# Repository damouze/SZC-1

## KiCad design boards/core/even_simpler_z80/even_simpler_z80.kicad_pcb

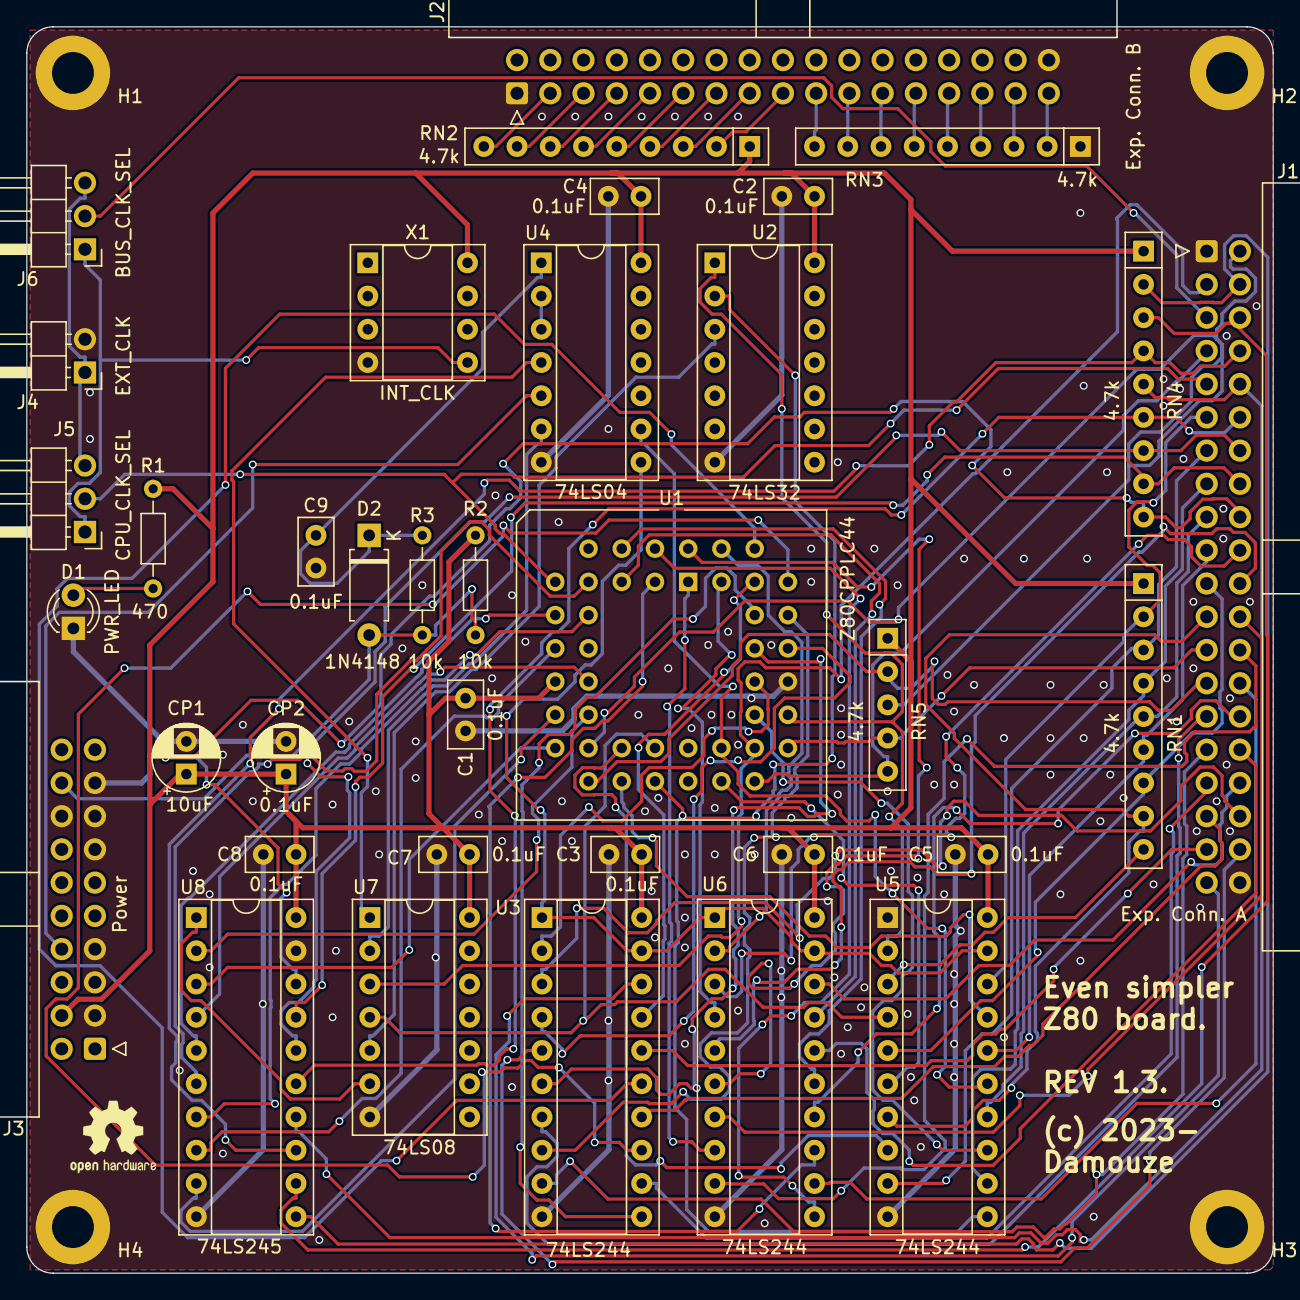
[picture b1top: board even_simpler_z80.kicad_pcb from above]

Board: 2 copper layers, 95.2 x 95.2 mm, 40 parts (0 on the bottom side), 101 nets.

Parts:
C1, C2, C3, C4, C5, C6, C7, C8, C9: 0.1uF; C_Disc_D5.0mm_W2.5mm_P2.50mm
CP1: 10uF; CP_Radial_D5.0mm_P2.50mm
CP2: 0.1uF; CP_Radial_D5.0mm_P2.50mm
D1: PWR_LED; LED_D3.0mm
D2: 1N4148; D_A-405_P7.62mm_Horizontal
H1, H2, H3, H4: MountingHole_Pad; MountingHole_3.2mm_M3_ISO7380_Pad
J1: Exp. Conn. A; IDC-Header_2x20_P2.54mm_Horizontal
J2: Exp. Conn. B; IDC-Header_2x17_P2.54mm_Horizontal
J3: Power; IDC-Header_2x10_P2.54mm_Horizontal
J4: EXT_CLK; PinHeader_1x02_P2.54mm_Horizontal
J5: CPU_CLK_SEL; PinHeader_1x03_P2.54mm_Horizontal
J6: BUS_CLK_SEL; PinHeader_1x03_P2.54mm_Horizontal
R1: 470; R_Axial_DIN0204_L3.6mm_D1.6mm_P7.62mm_Horizontal
R2, R3: 10k; R_Axial_DIN0204_L3.6mm_D1.6mm_P7.62mm_Horizontal
RN1, RN2, RN3, RN4: 4.7k; R_Array_SIP9
RN5: 4.7k; R_Array_SIP5
U1: Z80CPPLC44; PLCC-44_THT-Socket
U2: 74LS32; DIP-14_W7.62mm_Socket
U3, U5, U6: 74LS244; DIP-20_W7.62mm_Socket
U4: 74LS04; DIP-14_W7.62mm_Socket
U7: 74LS08; DIP-14_W7.62mm_Socket
U8: 74LS245; DIP-20_W7.62mm_Socket
X1: INT_CLK; DIP-8_W7.62mm_Socket

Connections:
/+5V: C1.1, C2.1, C3.1, C4.1, C5.1, C6.1, C7.1, C8.1, CP1.1, CP2.1, J3.4, R1.1, R2.1, RN1.1 (common), RN2.1 (common), RN4.1 (common), RN5.1 (common), U1.13 (VCC), U2.14 (VCC), U3.20 (VCC), U4.14 (VCC), U5.20 (VCC), U6.20 (VCC), U7.14 (VCC), U8.20 (VCC), X1.8 (Vcc)
/BUS_CLK: J1.5, J6.2
/B_A0: J1.39, U3.18 (O0a)
/B_A1: J1.37, U3.16 (O1a)
/B_A2: J1.35, U3.14 (O2a)
/B_A3: J1.33, U3.12 (O3a)
/B_A4: J1.31, U3.9 (O0b)
/B_A5: J1.29, U3.7 (O1b)
/B_A6: J1.38, U3.5 (O2b)
/B_A7: J1.36, U3.3 (O3b)
/B_A8: J1.34, U6.18 (O0a)
/B_A9: J1.32, U6.16 (O1a)
/B_A10: J1.30, U6.14 (O2a)
/B_A11: J1.28, U6.12 (O3a)
/B_A12: J1.26, U6.9 (O0b)
/B_A13: J1.24, U6.7 (O1b)
/B_A14: J1.22, U6.5 (O2b)
/B_A15: J1.20, U6.3 (O3b)
/B_D0: J1.18, RN4.9 (R8), U8.18 (B0)
/B_D1: J1.16, RN4.8 (R7), U8.17 (B1)
/B_D2: J1.14, RN4.7 (R6), U8.16 (B2)
/B_D3: J1.12, RN4.6 (R5), U8.15 (B3)
/B_D4: J1.10, RN4.5 (R4), U8.14 (B4)
/B_D5: J1.8, RN4.4 (R3), U8.13 (B5)
/B_D6: J1.6, RN4.3 (R2), U8.12 (B6)
/B_D7: J1.4, RN4.2 (R1), U8.11 (B7)
/CPU_CLK: J1.9, J5.2, U1.7 (~CLK)
/Clock & Reset circuit/EXT_CLK: J4.1, J5.3, J6.3
/Clock & Reset circuit/INT_CLK: J5.1, J6.1, X1.5 (OUT)
/Clock & Reset circuit/RESET1: U4.2, U4.3
/Clock & Reset circuit/~PWR_OK: U4.6, U7.2
/Clock & Reset circuit/~RESET1: U4.4, U7.1
/Clock & Reset circuit/~RESET_IN: C9.1, D2.1 (K), R3.1, U4.1
/GND: C1.2, C2.2, C3.2, C4.2, C5.2, C6.2, C7.2, C8.2, C9.2, CP1.2, CP2.2, D1.1 (K), H1.1, H2.1, H3.1, H4.1, J1.1, J1.40, J2.1, J2.34, J3.3, J3.5, J3.7, J3.13, J3.15, J3.16, J3.17, J4.2, RN3.1 (common), U1.33 (GND), U2.7 (GND), U3.10 (GND), U4.7 (GND), U5.1 (OEa), U5.10 (GND), U6.10 (GND), U7.7 (GND), U8.10 (GND), U8.19 (CE), X1.4 (GND)
/MCU/A0: U1.34 (A0), U3.2 (I0a)
/MCU/A1: U1.35 (A1), U3.4 (I1a)
/MCU/A2: U1.36 (A2), U3.6 (I2a)
/MCU/A3: U1.37 (A3), U3.8 (I3a)
/MCU/A4: U1.38 (A4), U3.11 (I0b)
/MCU/A5: U1.39 (A5), U3.13 (I1b)
/MCU/A6: U1.40 (A6), U3.15 (I2b)
/MCU/A7: U1.41 (A7), U3.17 (I3b)
/MCU/A8: U1.42 (A8), U6.2 (I0a)
/MCU/A9: U1.43 (A9), U6.4 (I1a)
/MCU/A10: U1.44 (A10), U6.6 (I2a)
/MCU/A11: U1.1 (A11), U6.8 (I3a)
/MCU/A12: U1.2 (A12), U6.11 (I0b)
/MCU/A13: U1.3 (A13), U6.13 (I1b)
/MCU/A14: U1.4 (A14), U6.15 (I2b)
/MCU/A15: U1.5 (A15), U6.17 (I3b)
/MCU/BUSACK: U3.1 (OEa), U3.19 (OEb), U4.8, U5.19 (OEb), U6.1 (OEa), U6.19 (OEb)
/MCU/D0: U1.16 (D0), U8.2 (A0)
/MCU/D1: U1.17 (D1), U8.3 (A1)
/MCU/D2: U1.14 (D2), U8.4 (A2)
/MCU/D3: U1.9 (D3), U8.5 (A3)
/MCU/D4: U1.8 (D4), U8.6 (A4)
/MCU/D5: U1.10 (D5), U8.7 (A5)
/MCU/D6: U1.11 (D6), U8.8 (A6)
/MCU/D7: U1.15 (D7), U8.9 (A7)
/MCU/~BUSACK: U1.27 (~BUSACK), U4.9, U5.15 (I2b)
/MCU/~BUSDIR: U7.6, U8.1 (A->B)
/MCU/~HALT: U1.20 (~HALT), U5.17 (I3b)
/MCU/~IORQ: U1.22 (~IORQ), U2.2, U5.11 (I0b)
/MCU/~M1: U1.31 (~M1), U2.1, U5.2 (I0a)
/MCU/~MREQ: U1.21 (~MREQ), U5.8 (I3a)
/MCU/~RD: U1.23 (~RD), U5.4 (I1a), U7.4
/MCU/~RFSH: U1.32 (~RFSH), U5.13 (I1b)
/MCU/~WR: U1.26 (~WR), U5.6 (I2a)
/M_A14: J2.33, RN3.2 (R1)
/M_A15: J2.31, RN3.3 (R2)
/M_A16: J2.29, RN3.4 (R3)
/M_A17: J2.27, RN3.5 (R4)
/M_A18: J2.25, RN3.6 (R5)
/M_A19: J2.23, RN3.7 (R6)
/M_A20: J2.21, RN3.8 (R7)
/M_A21: J2.19, RN3.9 (R8)
/PWR_OK: J3.8, U4.5
/~BUSREQ: J1.25, RN5.4 (R3), U1.29 (~BUSRQ)
/~B_BUSACK: J1.21, RN1.7 (R6), U5.5 (O2b)
/~B_HALT: RN1.9 (R8), U5.3 (O3b)
/~B_IORQ: J1.13, RN1.3 (R2), U5.9 (O0b)
/~B_M1: J1.11, RN1.2 (R1), U5.18 (O0a)
/~B_MREQ: J1.15, RN1.4 (R3), U5.12 (O3a)
/~B_RD: J1.19, RN1.6 (R5), U5.16 (O1a)
/~B_RFSH: J1.23, RN1.8 (R7), U5.7 (O1b)
/~B_WR: J1.17, RN1.5 (R4), U5.14 (O2a)
/~INT0: J2.17, RN2.2 (R1)
/~INT1: J2.15, RN2.3 (R2)
/~INT2: J2.13, RN2.4 (R3)
/~INT3: J2.11, RN2.5 (R4)
/~INT4: J2.9, RN2.6 (R5)
/~INT5: J2.7, RN2.7 (R6)
/~INT6: J2.5, RN2.8 (R7)
/~INT7: J2.3, RN2.9 (R8)
/~INTA: U2.3, U7.5
/~INT: J1.27, RN5.2 (R1), U1.18 (~INT)
/~NMI: J1.2, RN5.3 (R2), U1.19 (~NMI)
/~RESET_SW: D2.2 (A), J3.18, R2.2, R3.2
/~RESET: J1.3, U1.30 (~RESET), U7.3
/~WAIT: J1.7, RN5.5 (R4), U1.28 (~WAIT)
unnamed: D1.2 (A), R1.2

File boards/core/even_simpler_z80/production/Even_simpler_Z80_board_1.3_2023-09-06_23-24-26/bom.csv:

Designator,Footprint,Quantity,Value,LCSC Part #
"C1, C10, C2, C3, C4, C5, C6, C7, C8",C_Disc_D5.0mm_W2.5mm_P2.50mm,9,0.1uF,
CP1,CP_Radial_D5.0mm_P2.50mm,1,10uF,
CP2,CP_Radial_D5.0mm_P2.50mm,1,0.1uF,
D1,LED_D3.0mm,1,PWR_LED,
D2,D_A-405_P7.62mm_Horizontal,1,"1N4148
",
"H1, H2, H3, H4",MountingHole_3.2mm_M3_ISO7380_Pad,4,MountingHole_Pad,
J1,IDC-Header_2x20_P2.54mm_Horizontal,1,Exp. Conn. A,
J2,IDC-Header_2x17_P2.54mm_Horizontal,1,Exp. Conn. B,
J3,IDC-Header_2x10_P2.54mm_Horizontal,1,Power,
J4,PinHeader_1x02_P2.54mm_Horizontal,1,EXT_CLK,
J5,PinHeader_1x03_P2.54mm_Horizontal,1,CPU_CLK_SEL,
J6,PinHeader_1x03_P2.54mm_Horizontal,1,BUS_CLK_SEL,
R1,R_Axial_DIN0204_L3.6mm_D1.6mm_P7.62mm_Horizontal,1,1k,
"R2, R3",R_Axial_DIN0204_L3.6mm_D1.6mm_P7.62mm_Horizontal,2,10k,
"RN1, RN2, RN3, RN4",R_Array_SIP9,4,4.7k,
RN5,R_Array_SIP5,1,4.7k,
U1,PLCC-44_THT-Socket,1,Z80CPPLC44,
U2,DIP-14_W7.62mm_Socket,1,74LS32,
"U3, U5, U6",DIP-20_W7.62mm_Socket,3,74LS244,
U4,DIP-14_W7.62mm_Socket,1,74LS04,
U7,DIP-14_W7.62mm_Socket,1,74LS08,
U8,DIP-20_W7.62mm_Socket,1,74LS245,
X1,DIP-8_W7.62mm_Socket,1,INT_CLK,

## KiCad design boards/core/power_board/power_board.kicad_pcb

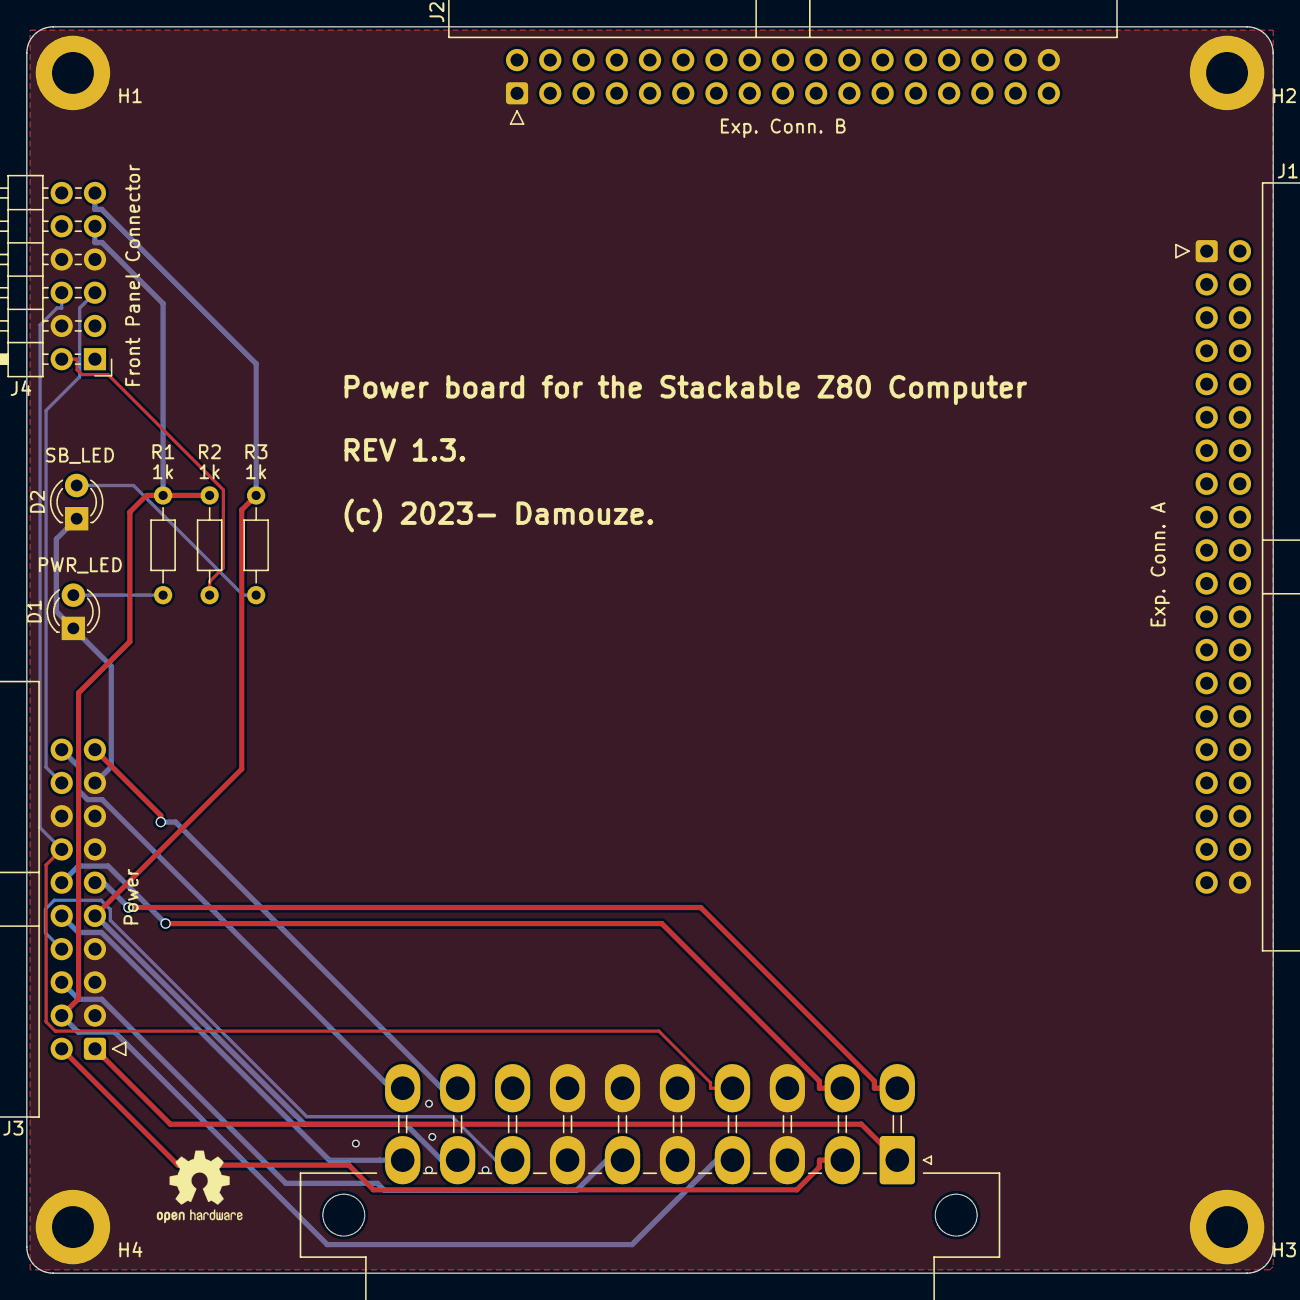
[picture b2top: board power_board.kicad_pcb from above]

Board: 2 copper layers, 95.2 x 95.2 mm, 14 parts (0 on the bottom side), 17 nets.

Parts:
D1: PWR_LED; LED_D3.0mm
D2: SB_LED; LED_D3.0mm
H1, H2, H3, H4: MountingHole_Pad; MountingHole_3.2mm_M3_ISO7380_Pad
J1: Exp. Conn. A; IDC-Header_2x20_P2.54mm_Horizontal
J2: Exp. Conn. B; IDC-Header_2x17_P2.54mm_Horizontal
J3: Power; IDC-Header_2x10_P2.54mm_Horizontal
J4: Front Panel Connector; PinHeader_2x06_P2.54mm_Horizontal
J5: ATX-20; Molex_Mini-Fit_Jr_5569-20A1_2x10_P4.20mm_Horizontal
R1, R2, R3: 1k; R_Axial_DIN0204_L3.6mm_D1.6mm_P7.62mm_Horizontal

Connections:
/+3.3V: J3.1, J5.1
/+3.3V2: J3.2, J5.2
/+3.3V3: J3.11, J5.11
/+5V: J3.4, J4.9, J5.4, R1.1, R2.1
/+5V2: J3.6, J5.6
/+5V3: J3.20, J5.20
/+5V4: J3.19, J5.19
/+5VSB: J3.9, J4.11, J5.9, R3.1
/+12V: J3.10, J5.10
/-12V: J3.12, J5.12
/GND: D1.1 (K), D2.1 (K), H1.1, H2.1, H3.1, H4.1, J1.1, J1.40, J2.1, J2.34, J3.3, J3.5, J3.7, J3.13, J3.15, J3.16, J3.17, J4.4, J4.7, J4.8, J5.3, J5.5, J5.7, J5.13, J5.15, J5.16, J5.17
/PWR_LED+: J4.2, R2.2
/PWR_OK: J3.8, J5.8
/~PS_ON: J3.14, J4.6, J5.14
/~RESET_SW: J3.18, J4.5
unnamed: D1.2 (A), R1.2
unnamed: D2.2 (A), R3.2

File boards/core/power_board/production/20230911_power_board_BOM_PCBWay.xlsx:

|  |  | xxxx xxxx xxxxx xxPCS BOM (Sample Bill of Materials)
Item # | *Designator | *Qty | Manufacturer | *Mfg Part # | Description / Value | *Package/Footprint | Type | Your Instructions / Notes
1 | D1 | 1 | Broadcom/AVAGO | HLMP-1700 | -40℃~+100℃ 626nm Red 14mW Plugin,D=3.2mm Light Emitting Diodes (LED) ROHS | LED_D3.0mm | thru-hole
2 | D2 | 1 | Broadcom/AVAGO | HLMP-1700 | -40℃~+100℃ 626nm Red 14mW Plugin,D=3.2mm Light Emitting Diodes (LED) ROHS | LED_D3.0mm | thru-hole
3 | H1, H2, H3, H4 | 4 | N/A | N/A | MountingHole_3.2mm_M3_ISO7380_Pad | N/A | N/A | Part of the board layout
4 | J1 | 1 | XKB Connectivity | X9555WR-2x20-6TV01 | 2x20P 2 Gold 2.54mm Male pin 2.54mm 20 260℃ -25℃~+85℃ Brass 3A Shrouded Push-Pu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 | IDC-Header_2x20_P2.54mm_Horizontal | thru-hole
5 | J2 | 1 | XKB Connectivity | X9555WR-2x17-6TV01 | 2x17P 2 Gold 2.54mm Male pin 2.54mm 17 260℃ -25℃~+85℃ Brass 3A Shrouded Push-Pu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 | IDC-Header_2x17_P2.54mm_Horizontal | thru-hole
6 | J3 | 1 | XKB Connectivity | X9555WR-2x10-6TV01 | 2x10P 2 Gold 2.54mm Male pin 2.54mm 10 260℃ -25℃~+85℃ Brass 3A Shrouded Push-Pu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 | IDC-Header_2x10_P2.54mm_Horizontal | thru-hole
7 | J4 | 1 | XFCN | PZ254R-12-12P | Shrouded Square Pins 2.5mm 12P 6mm -40℃~+105℃ 2.54mm 双排 Black Brass 2x6P 2.54mm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 | PinHeader_2x06_P2.54mm_Horizontal | thru-hole
8 | J5 | 1 | Molex | 39301200 | 2x10P 2 4.2mm Female pin 4.2mm 10 Shrouded Push-Pull,P=4.2mm Wire To Board / Wi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 | Molex_Mini-Fit_Jr_5569-20A1_2x10_P4.20mm_Horizontal | thru-hole
9 | R1, R2, R3 | 3 | YAGEO | MFR-25FRF52-1K | Metal Film Resistors 1kΩ 250mW ±100ppm/℃ ±1% Plugin Through Hole Resistors ROHS | R_Axial_DIN0204_L3.6mm_D1.6mm_P7.62mm_Horizontal | thru-hole
10
11
12
13
14
15
Need a quick and accurante quote? Need an efficient production? Please read SMT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
Click for Instructions on How to Create a BOM

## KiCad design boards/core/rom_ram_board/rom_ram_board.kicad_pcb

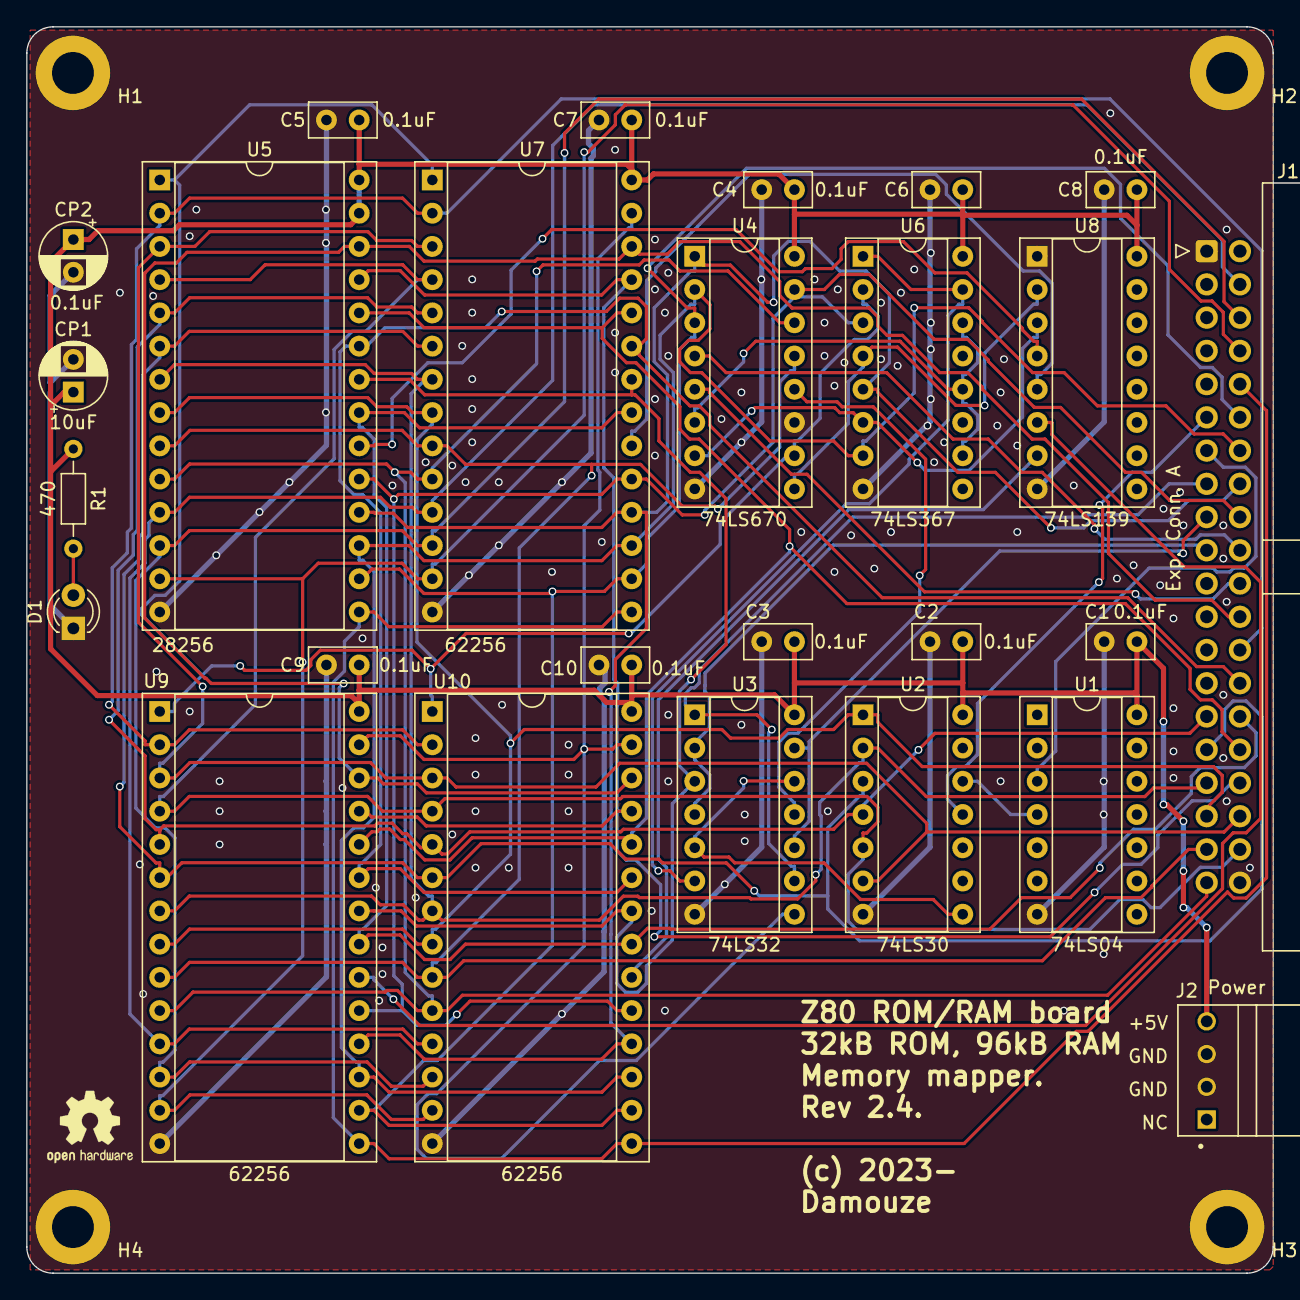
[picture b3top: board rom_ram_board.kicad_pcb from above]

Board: 2 copper layers, 95.2 x 95.2 mm, 30 parts (0 on the bottom side), 46 nets.

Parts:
C1, C2, C3, C4, C5, C6, C7, C8, C9, C10: 0.1uF; C_Disc_D5.0mm_W2.5mm_P2.50mm
CP1: 10uF; CP_Radial_D5.0mm_P2.50mm
CP2: 0.1uF; CP_Radial_D5.0mm_P2.50mm
D1: PWR_LED; LED_D3.0mm
H1, H2, H3, H4: MountingHole_Pad; MountingHole_3.2mm_M3_ISO7380_Pad
J1: Exp. Conn. A; IDC-Header_2x20_P2.54mm_Horizontal
J2: Power; TE_171826-4
R1: 470; R_Axial_DIN0204_L3.6mm_D1.6mm_P7.62mm_Horizontal
U1: 74LS04; DIP-14_W7.62mm_Socket
U2: 74LS30; DIP-14_W7.62mm_Socket
U3: 74LS32; DIP-14_W7.62mm_Socket
U4: 74LS670; DIP-16_W7.62mm_Socket
U5: 28256; DIP-28_W15.24mm_Socket
U6: 74LS367; DIP-16_W7.62mm_Socket
U7, U9, U10: 62256; DIP-28_W15.24mm_Socket
U8: 74LS139; DIP-16_W7.62mm_Socket

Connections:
/+5V: C1.1, C2.1, C3.1, C4.1, C5.1, C6.1, C7.1, C8.1, C9.1, C10.1, CP1.1, CP2.1, J2.4, R1.1, U1.14 (VCC), U2.14 (VCC), U3.14 (VCC), U4.16 (VCC), U5.27 (~WE), U5.28 (VCC), U6.16 (VCC), U7.28 (VCC), U8.16 (VCC), U9.28 (VCC), U10.28 (VCC)
/B_A0: J1.39, U4.14 (Wa), U5.10 (A0), U7.10 (A0), U9.10 (A0), U10.10 (A0)
/B_A1: J1.37, U4.13 (Wb), U5.9 (A1), U7.9 (A1), U9.9 (A1), U10.9 (A1)
/B_A2: J1.35, U2.1, U5.8 (A2), U7.8 (A2), U9.8 (A2), U10.8 (A2)
/B_A3: J1.33, U2.2, U5.7 (A3), U7.7 (A3), U9.7 (A3), U10.7 (A3)
/B_A4: J1.31, U2.3, U5.6 (A4), U7.6 (A4), U9.6 (A4), U10.6 (A4)
/B_A5: J1.29, U2.4, U5.5 (A5), U7.5 (A5), U9.5 (A5), U10.5 (A5)
/B_A6: J1.38, U2.5, U5.4 (A6), U7.4 (A6), U9.4 (A6), U10.4 (A6)
/B_A7: J1.36, U2.6, U5.3 (A7), U7.3 (A7), U9.3 (A7), U10.3 (A7)
/B_A8: J1.34, U5.25 (A8), U7.25 (A8), U9.25 (A8), U10.25 (A8)
/B_A9: J1.32, U5.24 (A9), U7.24 (A9), U9.24 (A9), U10.24 (A9)
/B_A10: J1.30, U5.21 (A10), U7.21 (A10), U9.21 (A10), U10.21 (A10)
/B_A11: J1.28, U5.23 (A11), U7.23 (A11), U9.23 (A11), U10.23 (A11)
/B_A12: J1.26, U5.2 (A12), U7.2 (A12), U9.2 (A12), U10.2 (A12)
/B_A13: J1.24, U5.26 (A13), U7.26 (A13), U9.26 (A13), U10.26 (A13)
/B_A14: J1.22, U4.5 (Ra)
/B_A15: J1.20, U4.4 (Rb)
/B_D0: J1.18, U4.15 (D1), U5.19 (D7), U6.3 (O1a), U7.19 (Q7), U9.19 (Q7), U10.19 (Q7)
/B_D1: J1.16, U4.1 (D2), U5.18 (D6), U6.5 (O2a), U7.18 (Q6), U9.18 (Q6), U10.18 (Q6)
/B_D2: J1.14, U4.2 (D3), U5.17 (D5), U6.7 (O3a), U7.17 (Q5), U9.17 (Q5), U10.17 (Q5)
/B_D3: J1.12, U4.3 (D4), U5.16 (D4), U7.16 (Q4), U9.16 (Q4), U10.16 (Q4)
/B_D4: J1.10, U5.15 (D3), U7.15 (Q3), U9.15 (Q3), U10.15 (Q3)
/B_D5: J1.8, U5.13 (D2), U7.13 (Q2), U9.13 (Q2), U10.13 (Q2)
/B_D6: J1.6, U5.12 (D1), U7.12 (Q1), U9.12 (Q1), U10.12 (Q1)
/B_D7: J1.4, U5.11 (D0), U7.11 (Q0), U9.11 (Q0), U10.11 (Q0)
/GND: C1.2, C2.2, C3.2, C4.2, C5.2, C6.2, C7.2, C8.2, C9.2, C10.2, CP1.2, CP2.2, D1.1 (K), H1.1, H2.1, H3.1, H4.1, J1.1, J1.40, J2.2, J2.3, U1.7 (GND), U2.7 (GND), U3.7 (GND), U4.8 (GND), U4.11 (~Er), U5.14 (GND), U6.8 (GND), U7.14 (GND), U8.1 (E), U8.8 (GND), U9.14 (GND), U10.14 (GND)
/IORQ: U1.4, U2.12
/R_A14: U4.10 (Q1), U5.1 (A14), U6.2 (I1), U7.1 (A14), U9.1 (A14), U10.1 (A14)
/R_A15: U4.9 (Q2), U6.4 (I2), U8.2 (A0)
/R_A16: U4.7 (Q3), U6.6 (I3), U8.3 (A1)
/~B_IORQ: J1.13, U1.3
/~B_M1: J1.11, U2.11
/~B_MREQ: J1.15, U3.1, U3.9
/~B_RD: J1.19, U3.2, U3.4
/~B_WR: J1.17, U3.10, U3.13
/~IO_RD: U3.6, U6.1 (OEa), U6.15 (OEb)
/~IO_WR: U3.11, U4.12 (~Ew)
/~MM_RD: U3.3, U5.22 (~OE), U7.22 (~OE), U9.22 (~OE), U10.22 (~OE)
/~MM_WR: U3.8, U7.27 (~WE), U9.27 (~WE), U10.27 (~WE)
/~RAM1_CS: U7.20 (~CS), U8.5 (O1)
/~RAM2_CS: U8.6 (O2), U9.20 (~CS)
/~RAM3_CS: U8.7 (O3), U10.20 (~CS)
/~ROM_CS: U5.20 (~CS), U8.4 (O0)
unnamed: D1.2 (A), R1.2
unnamed: U2.8, U3.5, U3.12
unnamed: U4.6 (Q4), U6.10 (I4), U6.12 (I5), U6.14 (I6)

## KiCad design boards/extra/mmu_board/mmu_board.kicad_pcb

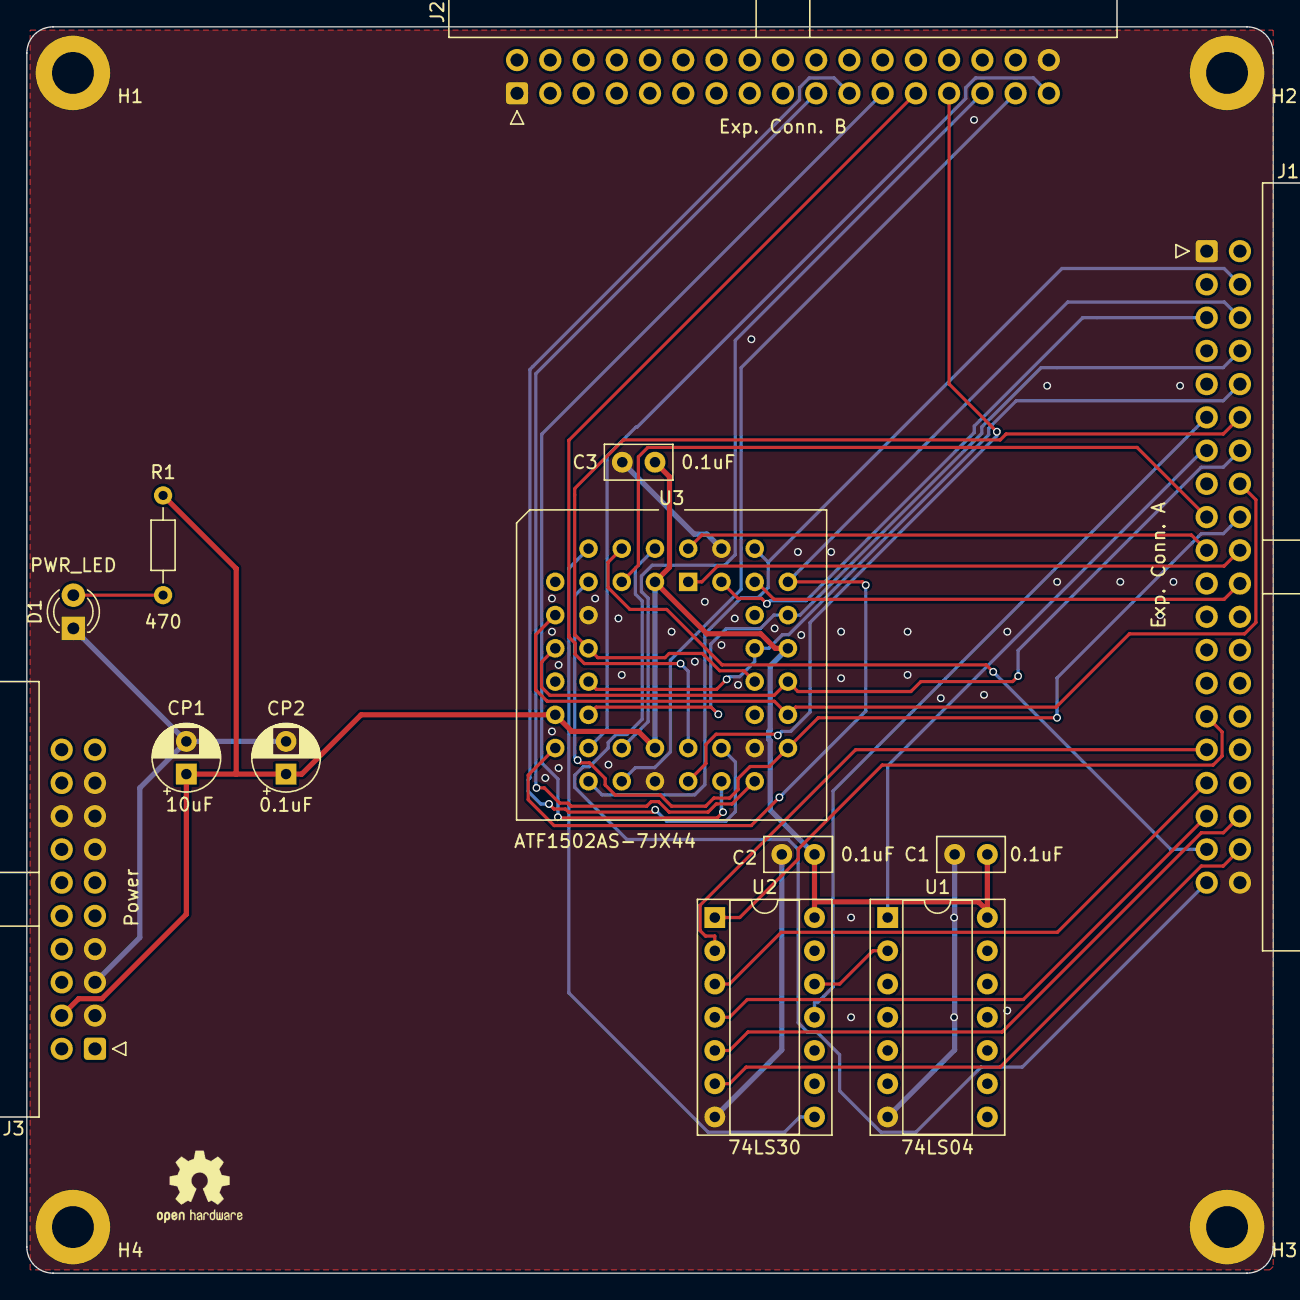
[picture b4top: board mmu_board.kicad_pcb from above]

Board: 2 copper layers, 95.2 x 95.2 mm, 17 parts (0 on the bottom side), 36 nets.

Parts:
C1, C2, C3: 0.1uF; C_Disc_D5.0mm_W2.5mm_P2.50mm
CP1: 10uF; CP_Radial_D5.0mm_P2.50mm
CP2: 0.1uF; CP_Radial_D5.0mm_P2.50mm
D1: PWR_LED; LED_D3.0mm
H1, H2, H3, H4: MountingHole_Pad; MountingHole_3.2mm_M3_ISO7380_Pad
J1: Exp. Conn. A; IDC-Header_2x20_P2.54mm_Horizontal
J2: Exp. Conn. B; IDC-Header_2x17_P2.54mm_Horizontal
J3: Power; IDC-Header_2x10_P2.54mm_Horizontal
R1: 470; R_Axial_DIN0204_L3.6mm_D1.6mm_P7.62mm_Horizontal
U1: 74LS04; DIP-14_W7.62mm_Socket
U2: 74LS30; DIP-14_W7.62mm_Socket
U3: ATF1502AS-7JX44; PLCC-44_THT-Socket

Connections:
/+5V: C1.1, C2.1, C3.1, CP1.1, CP2.1, J3.4, R1.1, U1.14 (VCC), U2.14 (VCC), U3.3 (VCC), U3.15 (VCC), U3.23 (VCC), U3.35 (VCC)
/BUS_CLK: J1.5, U3.43 (GCLK1/I)
/B_A0: J1.39, U3.2 (GCLK2/OE2/I)
/B_A1: J1.37, U3.4 (I/O)
/B_A2: J1.35, U2.4
/B_A3: J1.33, U2.3
/B_A4: J1.31, U2.2
/B_A5: J1.29, U2.1
/B_A6: J1.38, U2.6
/B_A7: J1.36, U2.5
/B_A14: J1.22, U3.41 (GCLK3/I/O)
/B_A15: J1.20, U3.1 (GCLR/I)
/B_D0: J1.18, U3.8 (I/O), U3.29 (I/O)
/B_D1: J1.16, U3.9 (I/O), U3.31 (I/O)
/B_D2: J1.14, U3.11 (PD1/I/O), U3.33 (I/O)
/B_D3: J1.12, U3.12 (I/O), U3.34 (I/O)
/B_D4: J1.10, U3.14 (I/O), U3.36 (I/O)
/B_D5: J1.8, U3.16 (I/O), U3.37 (I/O)
/B_D6: J1.6, U3.17 (I/O), U3.39 (I/O)
/B_D7: J1.4, U3.18 (I/O), U3.40 (I/O)
/GND: C1.2, C2.2, C3.2, CP1.2, CP2.2, D1.1 (K), H1.1, H2.1, H3.1, H4.1, J1.1, J1.40, J2.1, J2.34, J3.3, J3.5, J3.7, J3.13, J3.15, J3.16, J3.17, U1.7 (GND), U2.7 (GND), U3.10 (GND), U3.22 (GND), U3.30 (GND), U3.42 (GND)
/IORQ: U1.2, U2.12
/M_A14: J2.33, U3.19 (I/O)
/M_A15: J2.31, U3.20 (I/O)
/M_A16: J2.29, U3.21 (I/O)
/M_A17: J2.27, U3.24 (I/O)
/M_A18: J2.25, U3.25 (PD2/I/O)
/M_A19: J2.23, U3.26 (I/O)
/M_A20: J2.21, U3.27 (I/O)
/M_A21: J2.19, U3.28 (I/O)
/~B_IORQ: J1.13, U1.1
/~B_M1: J1.11, U2.11
/~B_RD: J1.19, U3.44 (OE1/I)
/~B_WR: J1.17, U3.5 (I/O)
/~MMU_CS: U2.8, U3.6 (I/O)
unnamed: D1.2 (A), R1.2

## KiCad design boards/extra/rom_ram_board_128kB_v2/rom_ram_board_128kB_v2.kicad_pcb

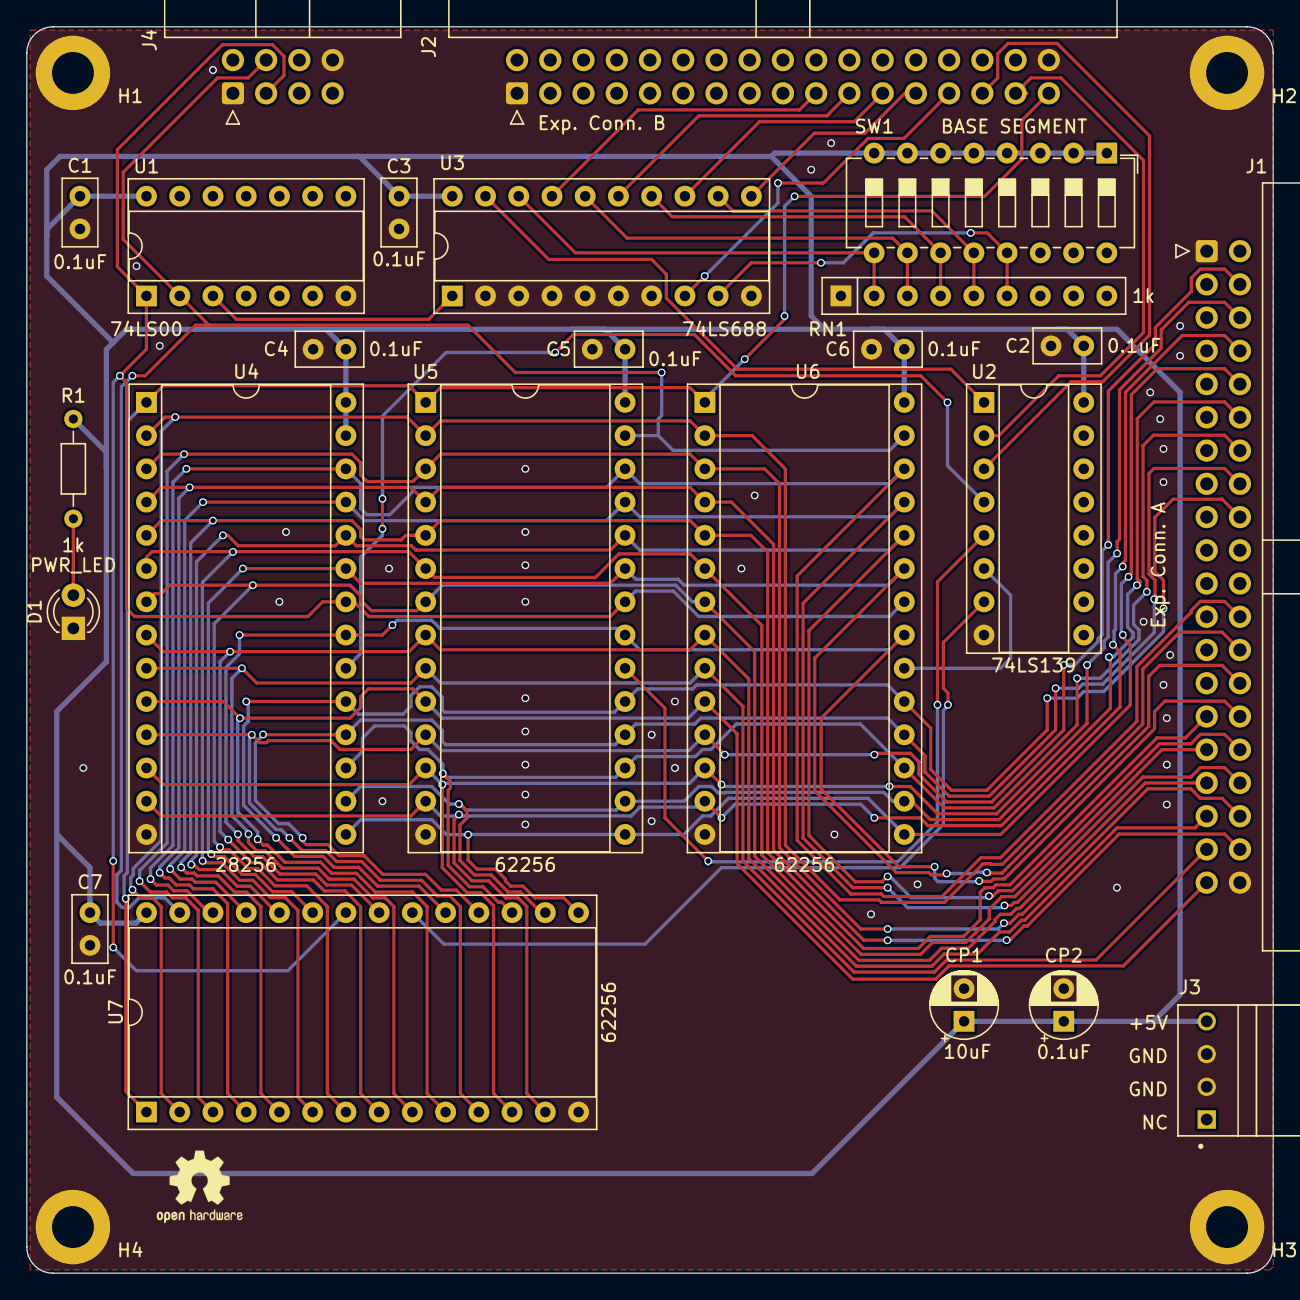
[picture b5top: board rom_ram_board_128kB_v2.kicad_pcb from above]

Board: 2 copper layers, 95.2 x 95.2 mm, 28 parts (0 on the bottom side), 46 nets.

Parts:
C1, C2, C3, C4, C5, C6, C7: 0.1uF; C_Disc_D5.0mm_W2.5mm_P2.50mm
CP1: 10uF; CP_Radial_D5.0mm_P2.50mm
CP2: 0.1uF; CP_Radial_D5.0mm_P2.50mm
D1: PWR_LED; LED_D3.0mm
H1, H2, H3, H4: MountingHole_Pad; MountingHole_3.2mm_M3_ISO7380_Pad
J1: Exp. Conn. A; IDC-Header_2x20_P2.54mm_Horizontal
J2: Exp. Conn. B; IDC-Header_2x17_P2.54mm_Horizontal
J3: Power; TE_171826-4
J4: Exp. Conn. C; IDC-Header_2x04_P2.54mm_Horizontal
R1: 1k; R_Axial_DIN0204_L3.6mm_D1.6mm_P7.62mm_Horizontal
RN1: 1k; R_Array_SIP9
SW1: BASE SEGMENT; SW_DIP_SPSTx08_Slide_6.7x21.88mm_W7.62mm_P2.54mm_LowProfile
U1: 74LS00; DIP-14_W7.62mm_Socket
U2: 74LS139; DIP-16_W7.62mm_Socket
U3: 74LS688; DIP-20_W7.62mm_Socket
U4: 28256; DIP-28_W15.24mm_Socket
U5, U6, U7: 62256; DIP-28_W15.24mm_Socket

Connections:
/+5V: C1.1, C2.1, C3.1, C4.1, C5.1, C6.1, C7.1, CP1.1, CP2.1, J3.4, R1.1, SW1.1, SW1.2, SW1.3, SW1.4, SW1.5, SW1.6, SW1.7, SW1.8, U1.14 (VCC), U2.16 (VCC), U3.20 (VCC), U4.27 (~WE), U4.28 (VCC), U5.28 (VCC), U6.28 (VCC), U7.28 (VCC)
/B_A0: J1.39, U4.10 (A0), U5.10 (A0), U6.10 (A0), U7.10 (A0)
/B_A1: J1.37, U4.9 (A1), U5.9 (A1), U6.9 (A1), U7.9 (A1)
/B_A2: J1.35, U4.8 (A2), U5.8 (A2), U6.8 (A2), U7.8 (A2)
/B_A3: J1.33, U4.7 (A3), U5.7 (A3), U6.7 (A3), U7.7 (A3)
/B_A4: J1.31, U4.6 (A4), U5.6 (A4), U6.6 (A4), U7.6 (A4)
/B_A5: J1.29, U4.5 (A5), U5.5 (A5), U6.5 (A5), U7.5 (A5)
/B_A6: J1.38, U4.4 (A6), U5.4 (A6), U6.4 (A6), U7.4 (A6)
/B_A7: J1.36, U4.3 (A7), U5.3 (A7), U6.3 (A7), U7.3 (A7)
/B_A8: J1.34, U4.25 (A8), U5.25 (A8), U6.25 (A8), U7.25 (A8)
/B_A9: J1.32, U4.24 (A9), U5.24 (A9), U6.24 (A9), U7.24 (A9)
/B_A10: J1.30, U4.21 (A10), U5.21 (A10), U6.21 (A10), U7.21 (A10)
/B_A11: J1.28, U4.23 (A11), U5.23 (A11), U6.23 (A11), U7.23 (A11)
/B_A12: J1.26, U4.2 (A12), U5.2 (A12), U6.2 (A12), U7.2 (A12)
/B_A13: J1.24, U4.26 (A13), U5.26 (A13), U6.26 (A13), U7.26 (A13)
/B_D0: J1.18, U4.19 (D7), U5.19 (Q7), U6.19 (Q7), U7.19 (Q7)
/B_D1: J1.16, U4.18 (D6), U5.18 (Q6), U6.18 (Q6), U7.18 (Q6)
/B_D2: J1.14, U4.17 (D5), U5.17 (Q5), U6.17 (Q5), U7.17 (Q5)
/B_D3: J1.12, U4.16 (D4), U5.16 (Q4), U6.16 (Q4), U7.16 (Q4)
/B_D4: J1.10, U4.15 (D3), U5.15 (Q3), U6.15 (Q3), U7.15 (Q3)
/B_D5: J1.8, U4.13 (D2), U5.13 (Q2), U6.13 (Q2), U7.13 (Q2)
/B_D6: J1.6, U4.12 (D1), U5.12 (Q1), U6.12 (Q1), U7.12 (Q1)
/B_D7: J1.4, U4.11 (D0), U5.11 (Q0), U6.11 (Q0), U7.11 (Q0)
/GND: C1.2, C2.2, C3.2, C4.2, C5.2, C6.2, C7.2, CP1.2, CP2.2, D1.1 (K), H1.1, H2.1, H3.1, H4.1, J1.1, J1.40, J2.1, J2.34, J3.2, J3.3, J4.1, J4.8, RN1.1 (common), U1.7 (GND), U2.8 (GND), U3.2 (P0), U3.3 (R0), U3.4 (P1), U3.5 (R1), U3.6 (P2), U3.7 (R2), U3.10 (GND), U4.14 (GND), U5.14 (GND), U6.14 (GND), U7.14 (GND)
/M_A14: J2.33, U4.1 (A14), U5.1 (A14), U6.1 (A14), U7.1 (A14)
/M_A15: J2.31, U2.2 (A0)
/M_A16: J2.29, U2.3 (A1)
/M_A17: J2.27, U3.8 (P3)
/M_A18: J2.25, U3.11 (P4)
/M_A19: J2.23, U3.13 (P5)
/M_A20: J2.21, U3.15 (P6)
/M_A21: J2.19, U3.17 (P7)
/R_A17: RN1.6 (R5), SW1.13, U3.9 (R3)
/R_A18: RN1.5 (R4), SW1.12, U3.12 (R4)
/R_A19: RN1.4 (R3), SW1.11, U3.14 (R5)
/R_A20: RN1.3 (R2), SW1.10, U3.16 (R6)
/R_A21: RN1.2 (R1), SW1.9, U3.18 (R7)
/~MEMR: J4.3, U1.1, U4.22 (~OE), U5.22 (~OE), U6.22 (~OE), U7.22 (~OE)
/~MEMW: J4.4, U1.2, U5.27 (~WE), U6.27 (~WE), U7.27 (~WE)
/~MEMXS: U1.3, U3.1 (G)
/~MEM_CS1: U2.4 (O0), U4.20 (~CS)
/~MEM_CS2: U2.5 (O1), U5.20 (~CS)
/~MEM_CS3: U2.6 (O2), U6.20 (~CS)
/~MEM_CS4: U2.7 (O3), U7.20 (~CS)
/~MEM_CS: U2.1 (E), U3.19 (P=R)
unnamed: D1.2 (A), R1.2

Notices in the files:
boards/core/even_simpler_z80/even_simpler_z80.kicad_pcb:
(c) 2023-
boards/core/power_board/power_board.kicad_pcb:
(c) 2023- Damouze.
boards/extra/rom_ram_board_128kB_v2/rom_ram_board_128kB_v2.kicad_pcb:
(c) 2024- Damouze
